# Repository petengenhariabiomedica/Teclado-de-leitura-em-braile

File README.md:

# Teclado-de-leitura-em-braile
Projeto de tecnologia assistiva voltado para pessoas cegas, consiste em um teclado que reproduzirá palavras da tela de um computador em letras em braile.

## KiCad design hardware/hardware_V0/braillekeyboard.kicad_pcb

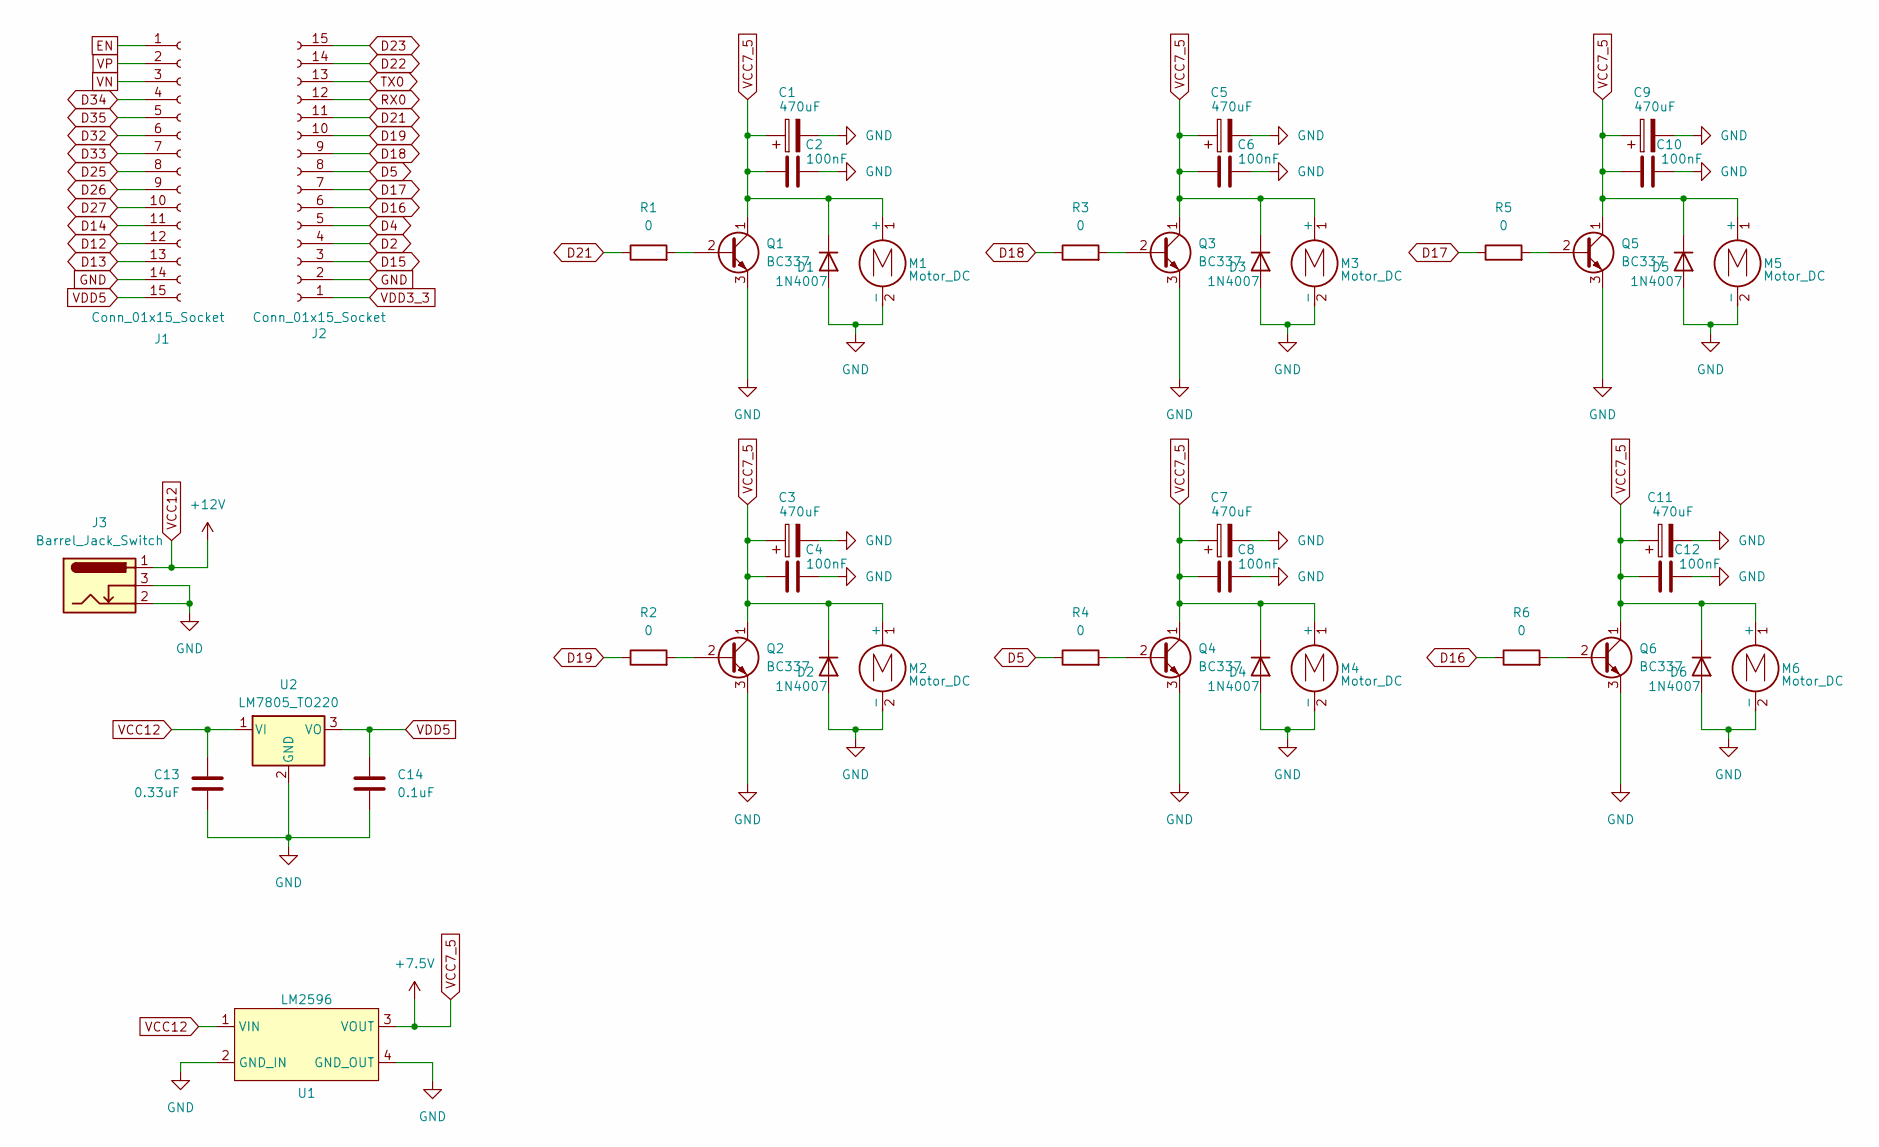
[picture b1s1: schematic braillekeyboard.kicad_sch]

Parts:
C1, C3, C5, C7, C9, C11: 470uF; CAPPRD500W60D1050H1750
C2, C4, C6, C8, C10, C12: 100nF; 615R100GAD10
C13: 0.33uF; CAPPRD350W60D825H1300
C14: 0.1uF; 615R100GAD10
D1, D2, D3, D4, D5, D6: 1N4007; D_DO-41_SOD81_P10.16mm_Horizontal
J1, J2: Conn_01x15_Socket; PinSocket_1x15_P2.54mm_Vertical
J3: Barrel_Jack_Switch; BarrelJack_Horizontal
M1, M2, M3, M4, M5, M6: Motor_DC; JST_XH_B2B-XH-AM_1x02_P2.50mm_Vertical
Q1, Q2, Q3, Q4, Q5, Q6: BC337; BC33716TA
R1, R2, R3, R4, R5, R6: 0; R_Axial_DIN0617_L17.0mm_D6.0mm_P25.40mm_Horizontal
U1: LM2596; LM2596_Module
U2: LM7805_TO220; TO-220-3_Vertical

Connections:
D2: J2.4
D4: J2.5
D5: J2.8, R4.1
D12: J1.12
D13: J1.13
D14: J1.11
D15: J2.3
D16: J2.6, R6.1
D17: J2.7, R5.1
D18: J2.9, R3.1
D19: J2.10, R2.1
D21: J2.11, R1.1
D22: J2.14
D23: J2.15
D25: J1.8
D26: J1.9
D27: J1.10
D32: J1.6
D33: J1.7
D34: J1.4
D35: J1.5
EN: J1.1
GND: C1.2, C2.2, C3.2, C4.2, C5.2, C6.2, C7.2, C8.2, C9.2, C10.2, C11.2, C12.2, C13.2, C14.2, D1.2 (A), D2.2 (A), D3.2 (A), D4.2 (A), D5.2 (A), D6.2 (A), J1.14, J2.2, J3.2, J3.3, M1.2 (-), M2.2 (-), M3.2 (-), M4.2 (-), M5.2 (-), M6.2 (-), Q1.3 (E), Q2.3 (E), Q3.3 (E), Q4.3 (E), Q5.3 (E), Q6.3 (E), U1.2 (GND_IN), U1.4 (GND_OUT), U2.2 (GND)
unnamed: Q1.2 (B), R1.2
unnamed: Q2.2 (B), R2.2
unnamed: Q3.2 (B), R3.2
unnamed: Q4.2 (B), R4.2
unnamed: Q5.2 (B), R5.2
unnamed: Q6.2 (B), R6.2
RX0: J2.12
TX0: J2.13
VCC7_5: C1.1, C2.1, C3.1, C4.1, C5.1, C6.1, C7.1, C8.1, C9.1, C10.1, C11.1, C12.1, D1.1 (K), D2.1 (K), D3.1 (K), D4.1 (K), D5.1 (K), D6.1 (K), M1.1 (+), M2.1 (+), M3.1 (+), M4.1 (+), M5.1 (+), M6.1 (+), Q1.1 (C), Q2.1 (C), Q3.1 (C), Q4.1 (C), Q5.1 (C), Q6.1 (C), U1.3 (VOUT)
VCC12: C13.1, J3.1, U1.1 (VIN), U2.1 (VI)
VDD3_3: J2.1
VDD5: C14.1, J1.15, U2.3 (VO)
VN: J1.3
VP: J1.2

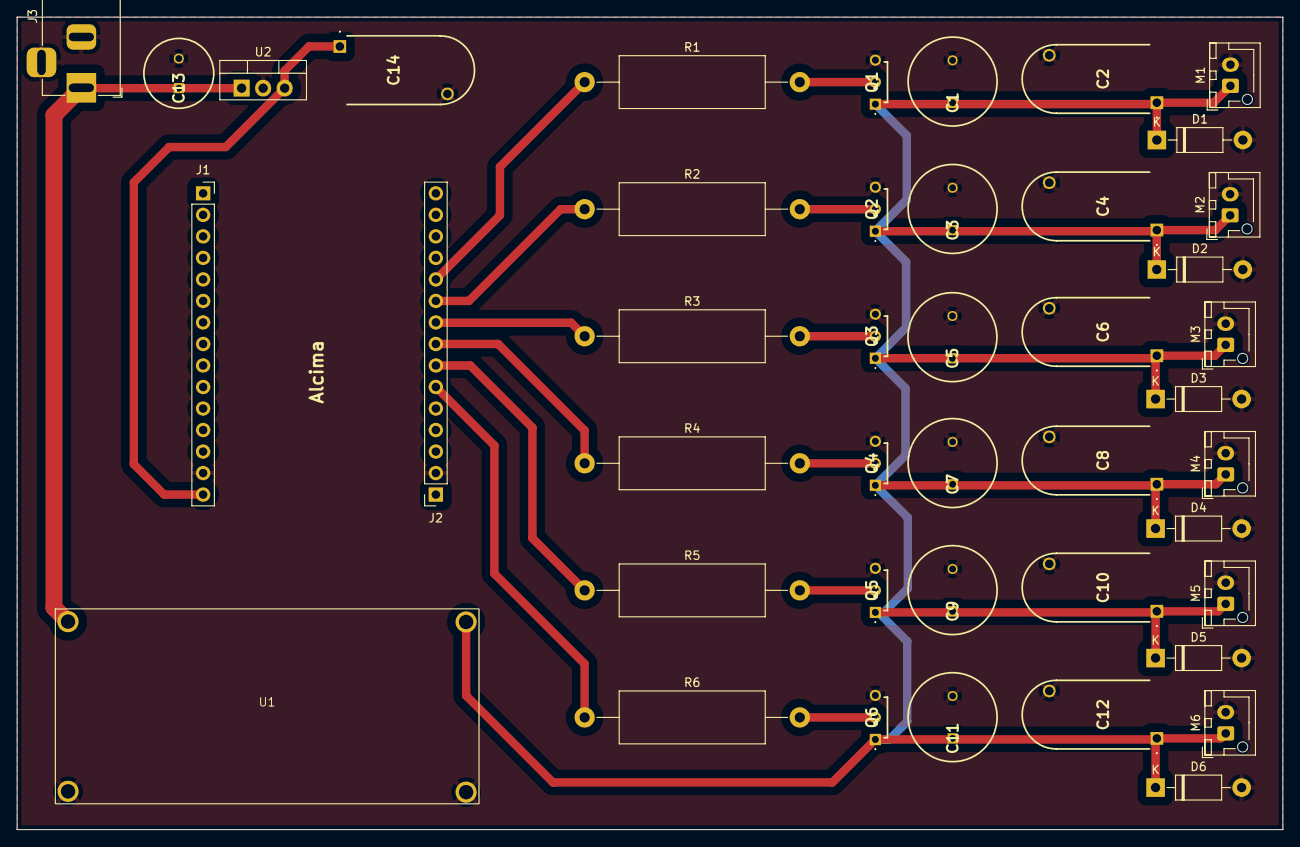
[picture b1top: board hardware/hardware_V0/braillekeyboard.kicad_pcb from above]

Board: 2 copper layers, 149.4 x 95.9 mm, 43 parts (0 on the bottom side), 16 nets.

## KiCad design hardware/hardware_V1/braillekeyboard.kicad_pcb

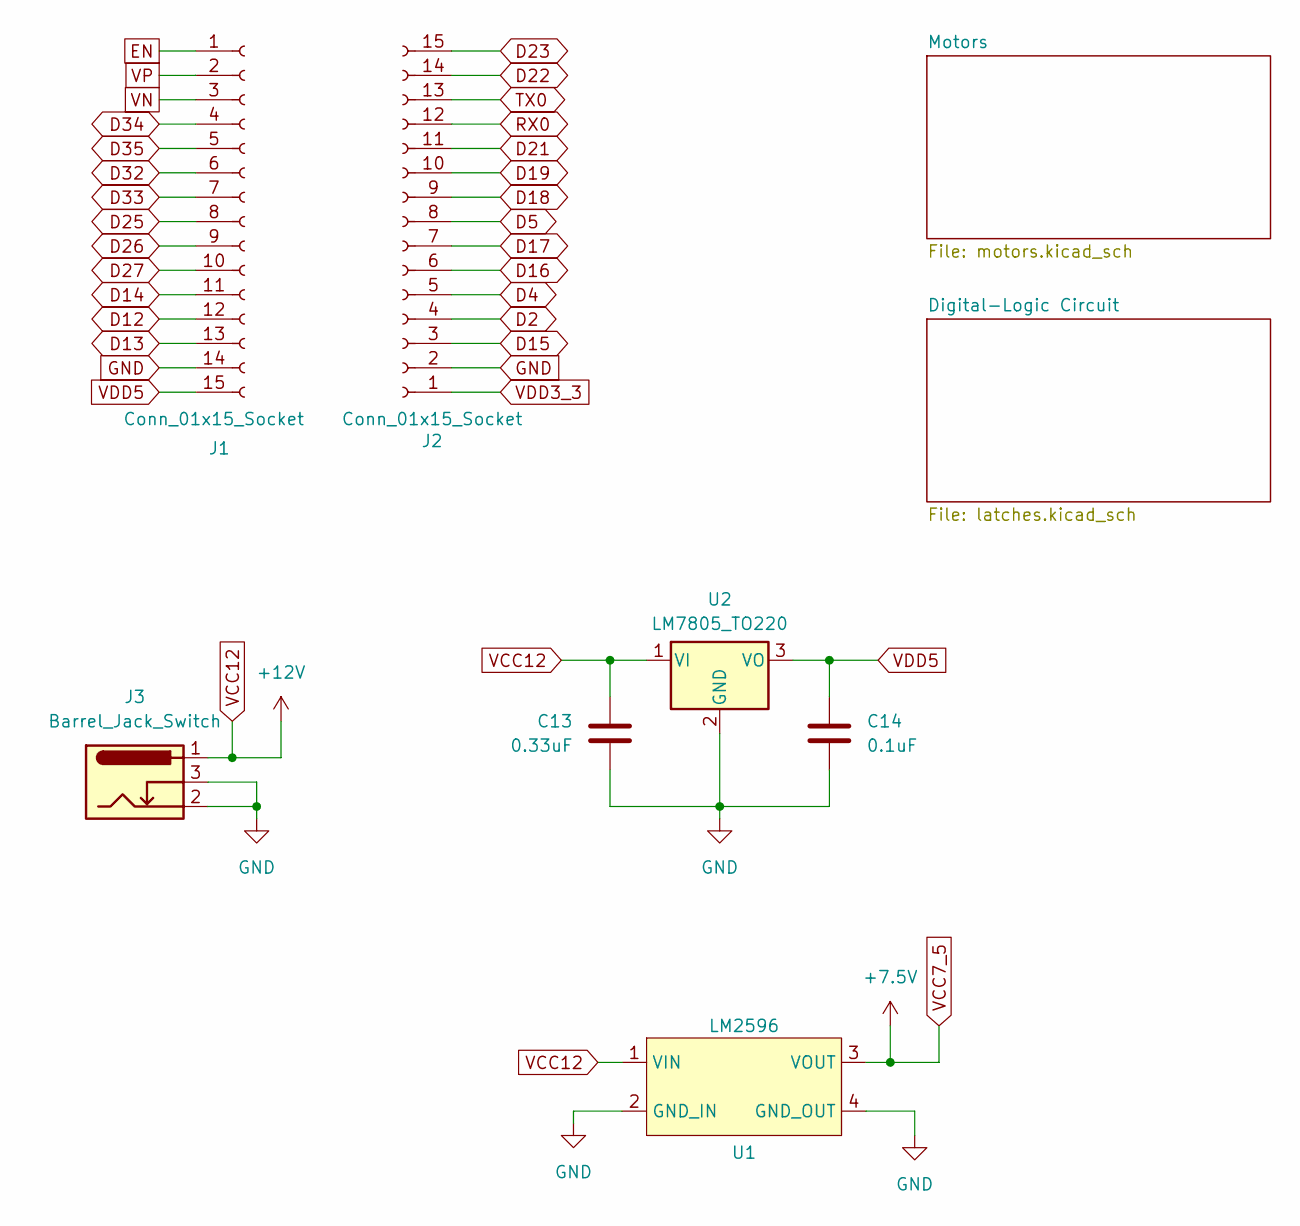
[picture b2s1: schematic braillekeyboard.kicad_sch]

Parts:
C13: 0.33uF; CAPPRD350W60D825H1300
C14: 0.1uF; 615R100GAD10
J1, J2: Conn_01x15_Socket; PinSocket_1x15_P2.54mm_Vertical
J3: Barrel_Jack_Switch; BarrelJack_Horizontal
U1: LM2596; LM2596_Module
U2: LM7805_TO220; TO-220-3_Vertical

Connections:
D2: J2.4; also elsewhere on the board
D4: J2.5; also elsewhere on the board
D5: J2.8; also elsewhere on the board
D12: J1.12; also elsewhere on the board
D13: J1.13; also elsewhere on the board
D14: J1.11; also elsewhere on the board
D15: J2.3; also elsewhere on the board
D16: J2.6; also elsewhere on the board
D17: J2.7; also elsewhere on the board
D18: J2.9; also elsewhere on the board
D19: J2.10; also elsewhere on the board
D21: J2.11; also elsewhere on the board
D22: J2.14
D23: J2.15
D25: J1.8; also elsewhere on the board
D26: J1.9; also elsewhere on the board
D27: J1.10; also elsewhere on the board
D32: J1.6
D33: J1.7; also elsewhere on the board
D34: J1.4
D35: J1.5
EN: J1.1
GND: C13.2, C14.2, J1.14, J2.2, J3.2, J3.3, U1.2 (GND_IN), U1.4 (GND_OUT), U2.2 (GND); also elsewhere on the board
RX0: J2.12
TX0: J2.13
VCC7_5: U1.3 (VOUT); also elsewhere on the board
VCC12: C13.1, J3.1, U1.1 (VIN), U2.1 (VI)
VDD3_3: J2.1
VDD5: C14.1, J1.15, U2.3 (VO); also elsewhere on the board
VN: J1.3
VP: J1.2

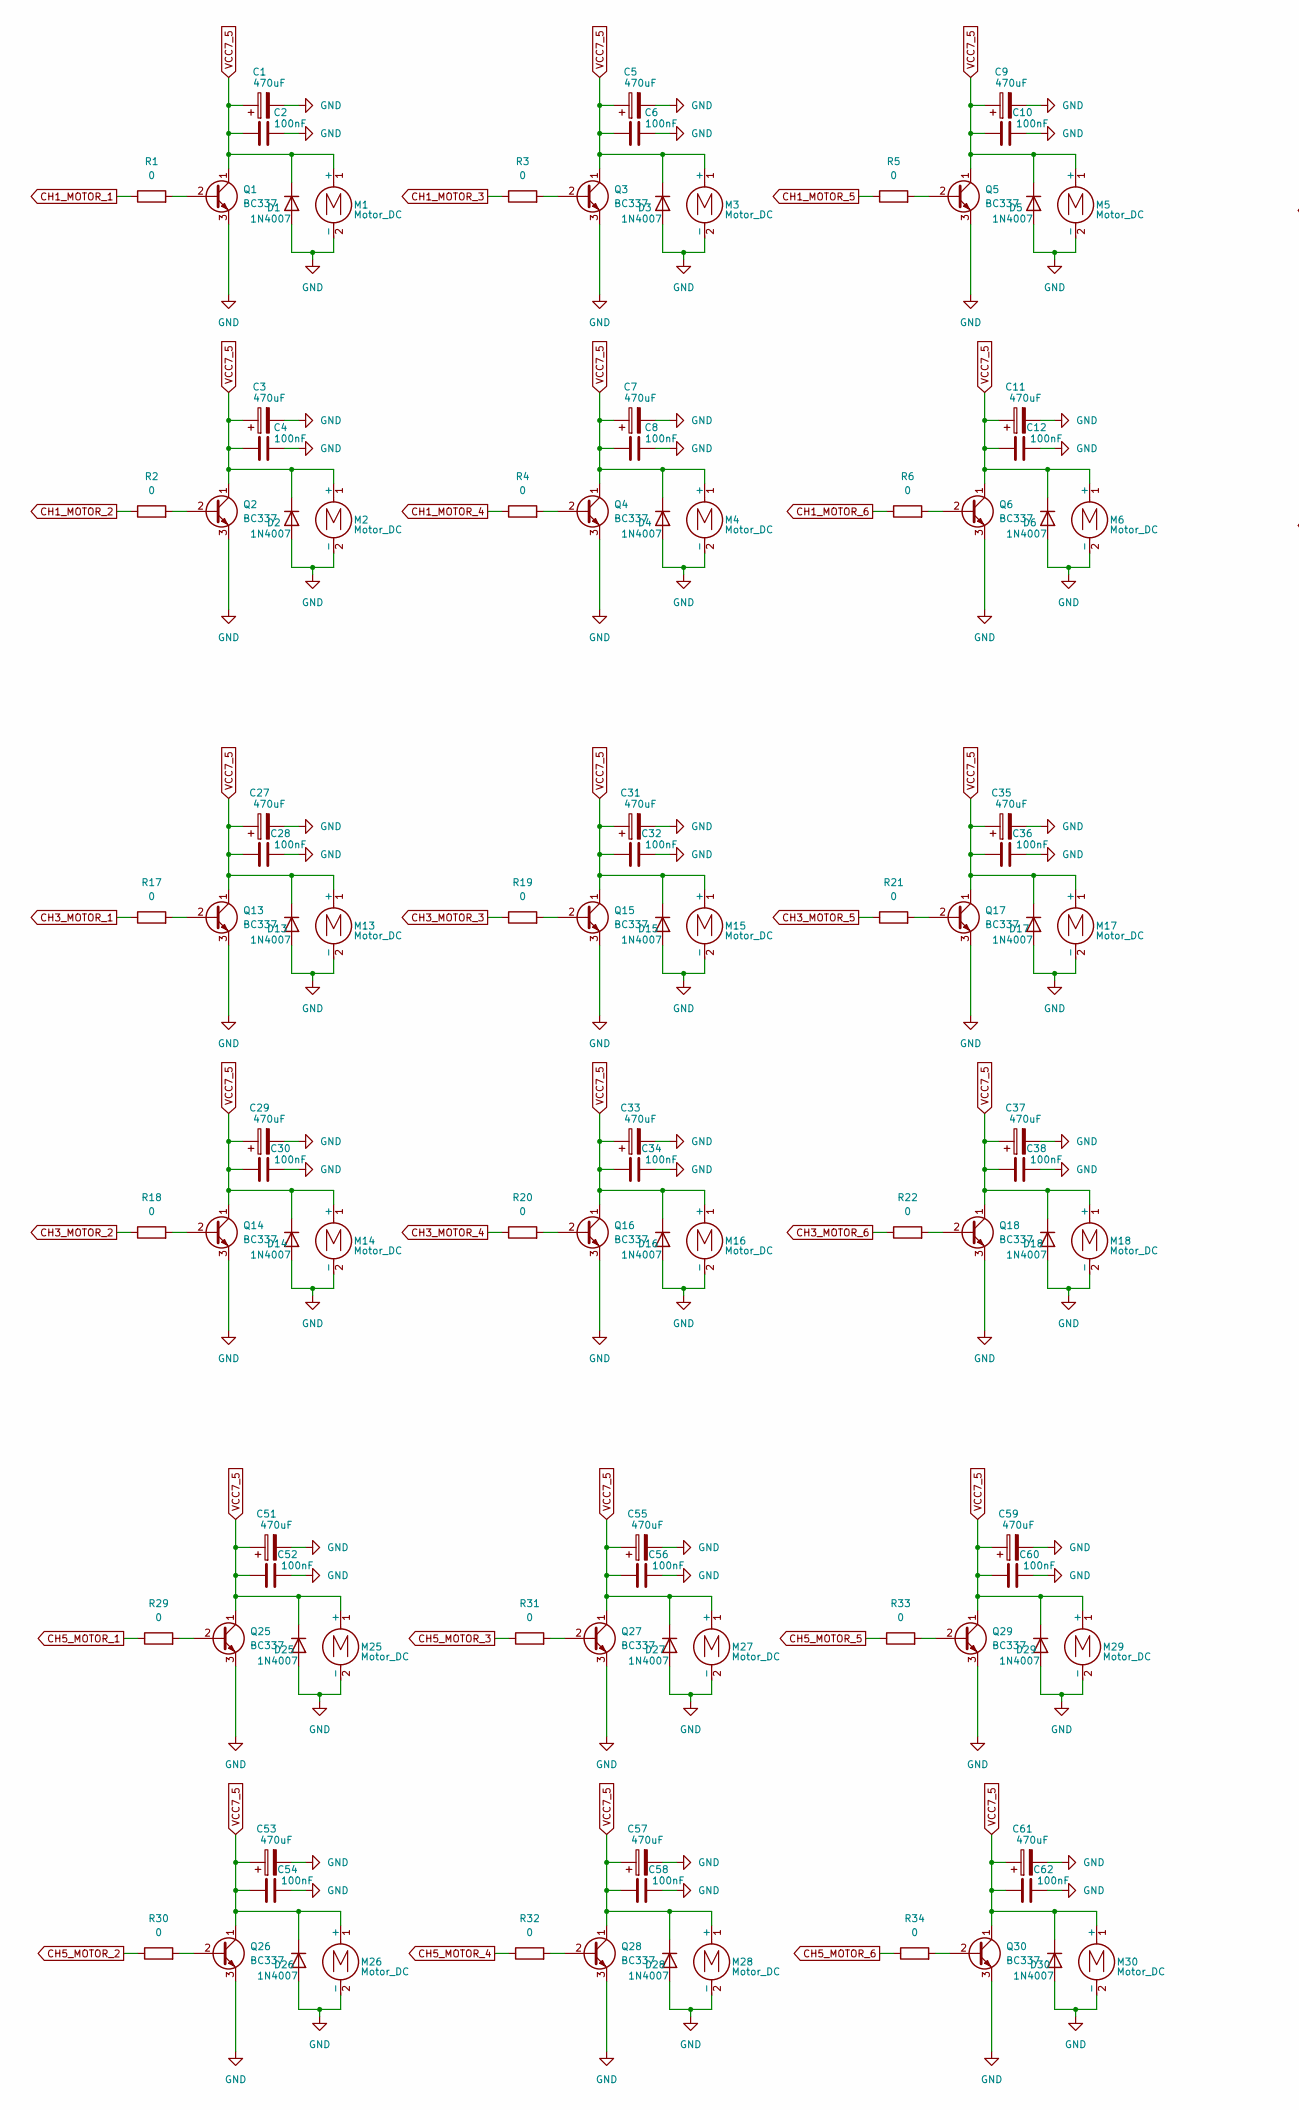
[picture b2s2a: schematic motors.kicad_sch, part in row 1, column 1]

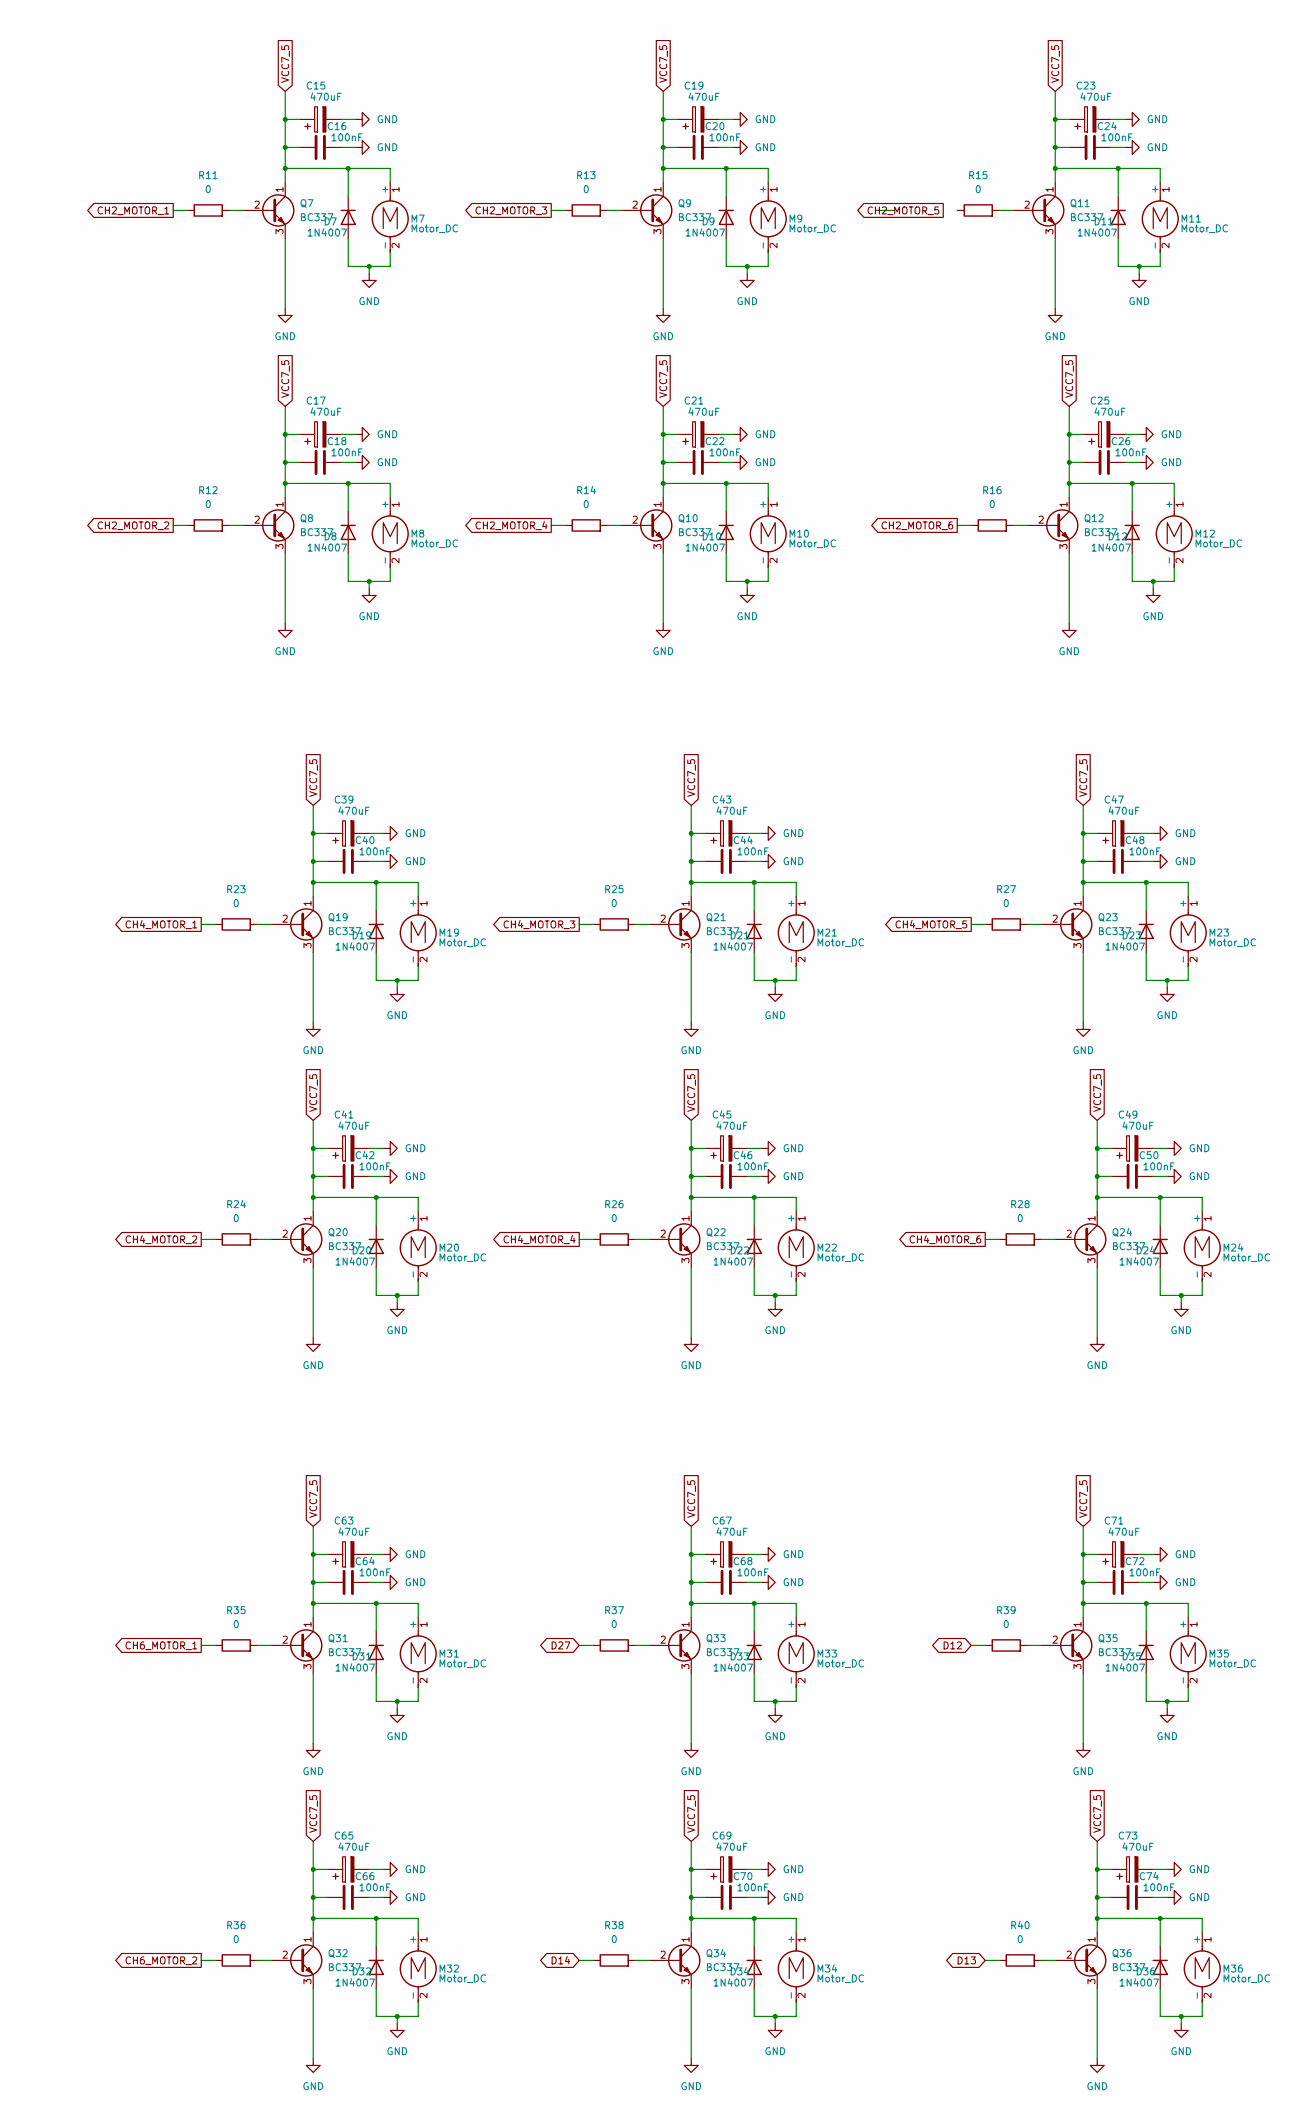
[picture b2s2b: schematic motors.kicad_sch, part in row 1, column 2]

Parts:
C1, C3, C5, C7, C9, C11, C15, C17, C19, C21, C23, C25, C27, C29, C31, C33, C35, C37, C39, C41, C43, C45, C47, C49, C51, C53, C55, C57, C59, C61, C63, C65, C67, C69, C71, C73: 470uF; CAPPRD500W60D1050H1750
C2, C4, C6, C8, C10, C12, C16, C18, C20, C22, C24, C26, C28, C30, C32, C34, C36, C38, C40, C42, C44, C46, C48, C50, C52, C54, C56, C58, C60, C62, C64, C66, C68, C70, C72, C74: 100nF; 615R100GAD10
D1, D2, D3, D4, D5, D6, D7, D8, D9, D10, D11, D12, D13, D14, D15, D16, D17, D18, D19, D20, D21, D22, D23, D24, D25, D26, D27, D28, D29, D30, D31, D32, D33, D34, D35, D36: 1N4007; D_DO-41_SOD81_P10.16mm_Horizontal
M1, M2, M3, M4, M5, M6, M7, M8, M9, M10, M11, M12, M13, M14, M15, M16, M17, M18, M19, M20, M21, M22, M23, M24, M25, M26, M27, M28, M29, M30, M31, M32, M33, M34, M35, M36: Motor_DC; JST_XH_B2B-XH-AM_1x02_P2.50mm_Vertical
Q1, Q2, Q3, Q4, Q5, Q6, Q7, Q8, Q9, Q10, Q11, Q12, Q13, Q14, Q15, Q16, Q17, Q18, Q19, Q20, Q21, Q22, Q23, Q24, Q25, Q26, Q27, Q28, Q29, Q30, Q31, Q32, Q33, Q34, Q35, Q36: BC337; BC33716TA
R1, R2, R3, R4, R5, R6, R11, R12, R13, R14, R15, R16, R17, R18, R19, R20, R21, R22, R23, R24, R25, R26, R27, R28, R29, R30, R31, R32, R33, R34, R35, R36, R37, R38, R39, R40: 0; R_Axial_DIN0617_L17.0mm_D6.0mm_P25.40mm_Horizontal

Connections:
CH1_MOTOR_1: R1.1; also elsewhere on the board
CH1_MOTOR_2: R2.1; also elsewhere on the board
CH1_MOTOR_3: R3.1; also elsewhere on the board
CH1_MOTOR_4: R4.1; also elsewhere on the board
CH1_MOTOR_5: R5.1; also elsewhere on the board
CH1_MOTOR_6: R6.1; also elsewhere on the board
CH2_MOTOR_1: R11.1; also elsewhere on the board
CH2_MOTOR_2: R12.1; also elsewhere on the board
CH2_MOTOR_3: R13.1; also elsewhere on the board
CH2_MOTOR_4: R14.1; also elsewhere on the board
CH2_MOTOR_6: R16.1; also elsewhere on the board
CH3_MOTOR_1: R17.1; also elsewhere on the board
CH3_MOTOR_2: R18.1; also elsewhere on the board
CH3_MOTOR_3: R19.1; also elsewhere on the board
CH3_MOTOR_4: R20.1; also elsewhere on the board
CH3_MOTOR_5: R21.1; also elsewhere on the board
CH3_MOTOR_6: R22.1; also elsewhere on the board
CH4_MOTOR_1: R23.1; also elsewhere on the board
CH4_MOTOR_2: R24.1; also elsewhere on the board
CH4_MOTOR_3: R25.1; also elsewhere on the board
CH4_MOTOR_4: R26.1; also elsewhere on the board
CH4_MOTOR_5: R27.1; also elsewhere on the board
CH4_MOTOR_6: R28.1; also elsewhere on the board
CH5_MOTOR_1: R29.1; also elsewhere on the board
CH5_MOTOR_2: R30.1; also elsewhere on the board
CH5_MOTOR_3: R31.1; also elsewhere on the board
CH5_MOTOR_4: R32.1; also elsewhere on the board
CH5_MOTOR_5: R33.1; also elsewhere on the board
CH5_MOTOR_6: R34.1; also elsewhere on the board
CH6_MOTOR_1: R35.1; also elsewhere on the board
CH6_MOTOR_2: R36.1; also elsewhere on the board
D12: R39.1; also elsewhere on the board
D13: R40.1; also elsewhere on the board
D14: R38.1; also elsewhere on the board
D27: R37.1; also elsewhere on the board
GND: C1.2, C2.2, C3.2, C4.2, C5.2, C6.2, C7.2, C8.2, C9.2, C10.2, C11.2, C12.2, C15.2, C16.2, C17.2, C18.2, C19.2, C20.2, C21.2, C22.2, C23.2, C24.2, C25.2, C26.2, C27.2, C28.2, C29.2, C30.2, C31.2, C32.2, C33.2, C34.2, C35.2, C36.2, C37.2, C38.2, C39.2, C40.2, C41.2, C42.2, C43.2, C44.2, C45.2, C46.2, C47.2, C48.2, C49.2, C50.2, C51.2, C52.2, C53.2, C54.2, C55.2, C56.2, C57.2, C58.2, C59.2, C60.2, C61.2, C62.2, C63.2, C64.2, C65.2, C66.2, C67.2, C68.2, C69.2, C70.2, C71.2, C72.2, C73.2, C74.2, D1.2 (A), D2.2 (A), D3.2 (A), D4.2 (A), D5.2 (A), D6.2 (A), D7.2 (A), D8.2 (A), D9.2 (A), D10.2 (A), D11.2 (A), D12.2 (A), D13.2 (A), D14.2 (A), D15.2 (A), D16.2 (A), D17.2 (A), D18.2 (A), D19.2 (A), D20.2 (A), D21.2 (A), D22.2 (A), D23.2 (A), D24.2 (A), D25.2 (A), D26.2 (A), D27.2 (A), D28.2 (A), D29.2 (A), D30.2 (A), D31.2 (A), D32.2 (A), D33.2 (A), D34.2 (A), D35.2 (A), D36.2 (A), M1.2 (-), M2.2 (-), M3.2 (-), M4.2 (-), M5.2 (-), M6.2 (-), M7.2 (-), M8.2 (-), M9.2 (-), M10.2 (-), M11.2 (-), M12.2 (-), M13.2 (-), M14.2 (-), M15.2 (-), M16.2 (-), M17.2 (-), M18.2 (-), M19.2 (-), M20.2 (-), M21.2 (-), M22.2 (-), M23.2 (-), M24.2 (-), M25.2 (-), M26.2 (-), M27.2 (-), M28.2 (-), M29.2 (-), M30.2 (-), M31.2 (-), M32.2 (-), M33.2 (-), M34.2 (-), M35.2 (-), M36.2 (-), Q1.3 (E), Q2.3 (E), Q3.3 (E), Q4.3 (E), Q5.3 (E), Q6.3 (E), Q7.3 (E), Q8.3 (E), Q9.3 (E), Q10.3 (E), Q11.3 (E), Q12.3 (E), Q13.3 (E), Q14.3 (E), Q15.3 (E), Q16.3 (E), Q17.3 (E), Q18.3 (E), Q19.3 (E), Q20.3 (E), Q21.3 (E), Q22.3 (E), Q23.3 (E), Q24.3 (E), Q25.3 (E), Q26.3 (E), Q27.3 (E), Q28.3 (E), Q29.3 (E), Q30.3 (E), Q31.3 (E), Q32.3 (E), Q33.3 (E), Q34.3 (E), Q35.3 (E), Q36.3 (E); also elsewhere on the board
unnamed: Q1.2 (B), R1.2
unnamed: Q2.2 (B), R2.2
unnamed: Q3.2 (B), R3.2
unnamed: Q4.2 (B), R4.2
unnamed: Q5.2 (B), R5.2
unnamed: Q6.2 (B), R6.2
unnamed: Q7.2 (B), R11.2
unnamed: Q8.2 (B), R12.2
unnamed: Q9.2 (B), R13.2
unnamed: Q10.2 (B), R14.2
unnamed: Q11.2 (B), R15.2
unnamed: Q12.2 (B), R16.2
unnamed: Q13.2 (B), R17.2
unnamed: Q14.2 (B), R18.2
unnamed: Q15.2 (B), R19.2
unnamed: Q16.2 (B), R20.2
unnamed: Q17.2 (B), R21.2
unnamed: Q18.2 (B), R22.2
unnamed: Q19.2 (B), R23.2
unnamed: Q20.2 (B), R24.2
unnamed: Q21.2 (B), R25.2
unnamed: Q22.2 (B), R26.2
unnamed: Q23.2 (B), R27.2
unnamed: Q24.2 (B), R28.2
unnamed: Q25.2 (B), R29.2
unnamed: Q26.2 (B), R30.2
unnamed: Q27.2 (B), R31.2
unnamed: Q28.2 (B), R32.2
unnamed: Q29.2 (B), R33.2
unnamed: Q30.2 (B), R34.2
unnamed: Q31.2 (B), R35.2
unnamed: Q32.2 (B), R36.2
unnamed: Q33.2 (B), R37.2
unnamed: Q34.2 (B), R38.2
unnamed: Q35.2 (B), R39.2
unnamed: Q36.2 (B), R40.2
VCC7_5: C1.1, C2.1, C3.1, C4.1, C5.1, C6.1, C7.1, C8.1, C9.1, C10.1, C11.1, C12.1, C15.1, C16.1, C17.1, C18.1, C19.1, C20.1, C21.1, C22.1, C23.1, C24.1, C25.1, C26.1, C27.1, C28.1, C29.1, C30.1, C31.1, C32.1, C33.1, C34.1, C35.1, C36.1, C37.1, C38.1, C39.1, C40.1, C41.1, C42.1, C43.1, C44.1, C45.1, C46.1, C47.1, C48.1, C49.1, C50.1, C51.1, C52.1, C53.1, C54.1, C55.1, C56.1, C57.1, C58.1, C59.1, C60.1, C61.1, C62.1, C63.1, C64.1, C65.1, C66.1, C67.1, C68.1, C69.1, C70.1, C71.1, C72.1, C73.1, C74.1, D1.1 (K), D2.1 (K), D3.1 (K), D4.1 (K), D5.1 (K), D6.1 (K), D7.1 (K), D8.1 (K), D9.1 (K), D10.1 (K), D11.1 (K), D12.1 (K), D13.1 (K), D14.1 (K), D15.1 (K), D16.1 (K), D17.1 (K), D18.1 (K), D19.1 (K), D20.1 (K), D21.1 (K), D22.1 (K), D23.1 (K), D24.1 (K), D25.1 (K), D26.1 (K), D27.1 (K), D28.1 (K), D29.1 (K), D30.1 (K), D31.1 (K), D32.1 (K), D33.1 (K), D34.1 (K), D35.1 (K), D36.1 (K), M1.1 (+), M2.1 (+), M3.1 (+), M4.1 (+), M5.1 (+), M6.1 (+), M7.1 (+), M8.1 (+), M9.1 (+), M10.1 (+), M11.1 (+), M12.1 (+), M13.1 (+), M14.1 (+), M15.1 (+), M16.1 (+), M17.1 (+), M18.1 (+), M19.1 (+), M20.1 (+), M21.1 (+), M22.1 (+), M23.1 (+), M24.1 (+), M25.1 (+), M26.1 (+), M27.1 (+), M28.1 (+), M29.1 (+), M30.1 (+), M31.1 (+), M32.1 (+), M33.1 (+), M34.1 (+), M35.1 (+), M36.1 (+), Q1.1 (C), Q2.1 (C), Q3.1 (C), Q4.1 (C), Q5.1 (C), Q6.1 (C), Q7.1 (C), Q8.1 (C), Q9.1 (C), Q10.1 (C), Q11.1 (C), Q12.1 (C), Q13.1 (C), Q14.1 (C), Q15.1 (C), Q16.1 (C), Q17.1 (C), Q18.1 (C), Q19.1 (C), Q20.1 (C), Q21.1 (C), Q22.1 (C), Q23.1 (C), Q24.1 (C), Q25.1 (C), Q26.1 (C), Q27.1 (C), Q28.1 (C), Q29.1 (C), Q30.1 (C), Q31.1 (C), Q32.1 (C), Q33.1 (C), Q34.1 (C), Q35.1 (C), Q36.1 (C); also elsewhere on the board

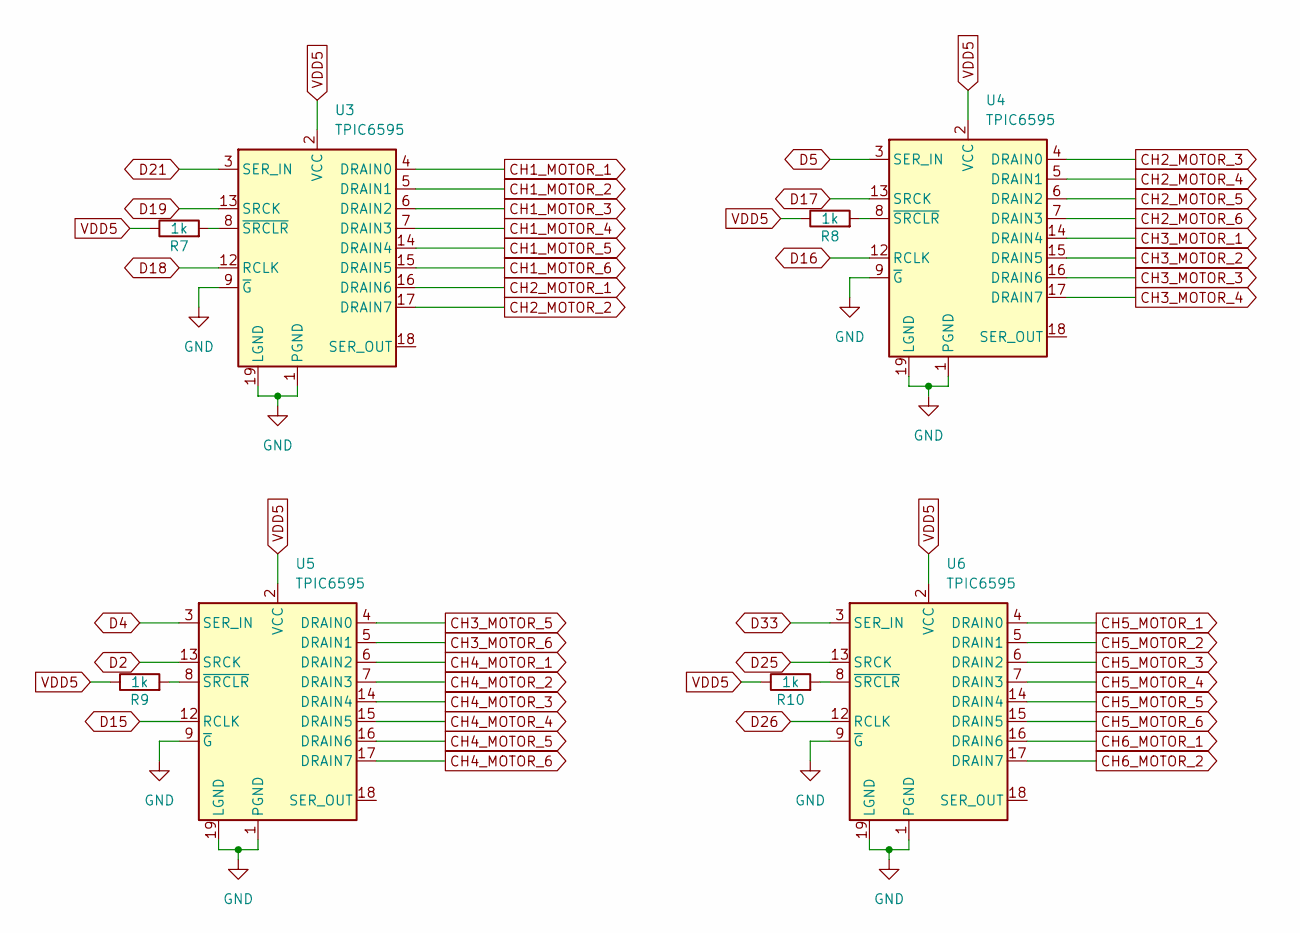
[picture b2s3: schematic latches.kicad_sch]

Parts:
R7, R8, R9, R10: 1k; R_Axial_DIN0617_L17.0mm_D6.0mm_P25.40mm_Horizontal
U3, U4, U5, U6: TPIC6595; DIP794W53P254L2540H508Q20N

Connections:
CH1_MOTOR_1: U3.4 (DRAIN0); also elsewhere on the board
CH1_MOTOR_2: U3.5 (DRAIN1); also elsewhere on the board
CH1_MOTOR_3: U3.6 (DRAIN2); also elsewhere on the board
CH1_MOTOR_4: U3.7 (DRAIN3); also elsewhere on the board
CH1_MOTOR_5: U3.14 (DRAIN4); also elsewhere on the board
CH1_MOTOR_6: U3.15 (DRAIN5); also elsewhere on the board
CH2_MOTOR_1: U3.16 (DRAIN6); also elsewhere on the board
CH2_MOTOR_2: U3.17 (DRAIN7); also elsewhere on the board
CH2_MOTOR_3: U4.4 (DRAIN0); also elsewhere on the board
CH2_MOTOR_4: U4.5 (DRAIN1); also elsewhere on the board
CH2_MOTOR_5: U4.6 (DRAIN2)
CH2_MOTOR_6: U4.7 (DRAIN3); also elsewhere on the board
CH3_MOTOR_1: U4.14 (DRAIN4); also elsewhere on the board
CH3_MOTOR_2: U4.15 (DRAIN5); also elsewhere on the board
CH3_MOTOR_3: U4.16 (DRAIN6); also elsewhere on the board
CH3_MOTOR_4: U4.17 (DRAIN7); also elsewhere on the board
CH3_MOTOR_5: U5.4 (DRAIN0); also elsewhere on the board
CH3_MOTOR_6: U5.5 (DRAIN1); also elsewhere on the board
CH4_MOTOR_1: U5.6 (DRAIN2); also elsewhere on the board
CH4_MOTOR_2: U5.7 (DRAIN3); also elsewhere on the board
CH4_MOTOR_3: U5.14 (DRAIN4); also elsewhere on the board
CH4_MOTOR_4: U5.15 (DRAIN5); also elsewhere on the board
CH4_MOTOR_5: U5.16 (DRAIN6); also elsewhere on the board
CH4_MOTOR_6: U5.17 (DRAIN7); also elsewhere on the board
CH5_MOTOR_1: U6.4 (DRAIN0); also elsewhere on the board
CH5_MOTOR_2: U6.5 (DRAIN1); also elsewhere on the board
CH5_MOTOR_3: U6.6 (DRAIN2); also elsewhere on the board
CH5_MOTOR_4: U6.7 (DRAIN3); also elsewhere on the board
CH5_MOTOR_5: U6.14 (DRAIN4); also elsewhere on the board
CH5_MOTOR_6: U6.15 (DRAIN5); also elsewhere on the board
CH6_MOTOR_1: U6.16 (DRAIN6); also elsewhere on the board
CH6_MOTOR_2: U6.17 (DRAIN7); also elsewhere on the board
D2: U5.13 (SRCK); also elsewhere on the board
D4: U5.3 (SER_IN); also elsewhere on the board
D5: U4.3 (SER_IN); also elsewhere on the board
D15: U5.12 (RCLK); also elsewhere on the board
D16: U4.12 (RCLK); also elsewhere on the board
D17: U4.13 (SRCK); also elsewhere on the board
D18: U3.12 (RCLK); also elsewhere on the board
D19: U3.13 (SRCK); also elsewhere on the board
D21: U3.3 (SER_IN); also elsewhere on the board
D25: U6.13 (SRCK); also elsewhere on the board
D26: U6.12 (RCLK); also elsewhere on the board
D33: U6.3 (SER_IN); also elsewhere on the board
GND: U3.1 (PGND), U3.9 (~G), U3.10 (PGND), U3.11 (PGND), U3.19 (LGND), U3.20 (PGND), U4.1 (PGND), U4.9 (~G), U4.10 (PGND), U4.11 (PGND), U4.19 (LGND), U4.20 (PGND), U5.1 (PGND), U5.9 (~G), U5.10 (PGND), U5.11 (PGND), U5.19 (LGND), U5.20 (PGND), U6.1 (PGND), U6.9 (~G), U6.10 (PGND), U6.11 (PGND), U6.19 (LGND), U6.20 (PGND); also elsewhere on the board
unnamed: R7.2, U3.8 (~SRCLR)
unnamed: R8.2, U4.8 (~SRCLR)
unnamed: R9.2, U5.8 (~SRCLR)
unnamed: R10.2, U6.8 (~SRCLR)
VDD5: R7.1, R8.1, R9.1, R10.1, U3.2 (VCC), U4.2 (VCC), U5.2 (VCC), U6.2 (VCC); also elsewhere on the board

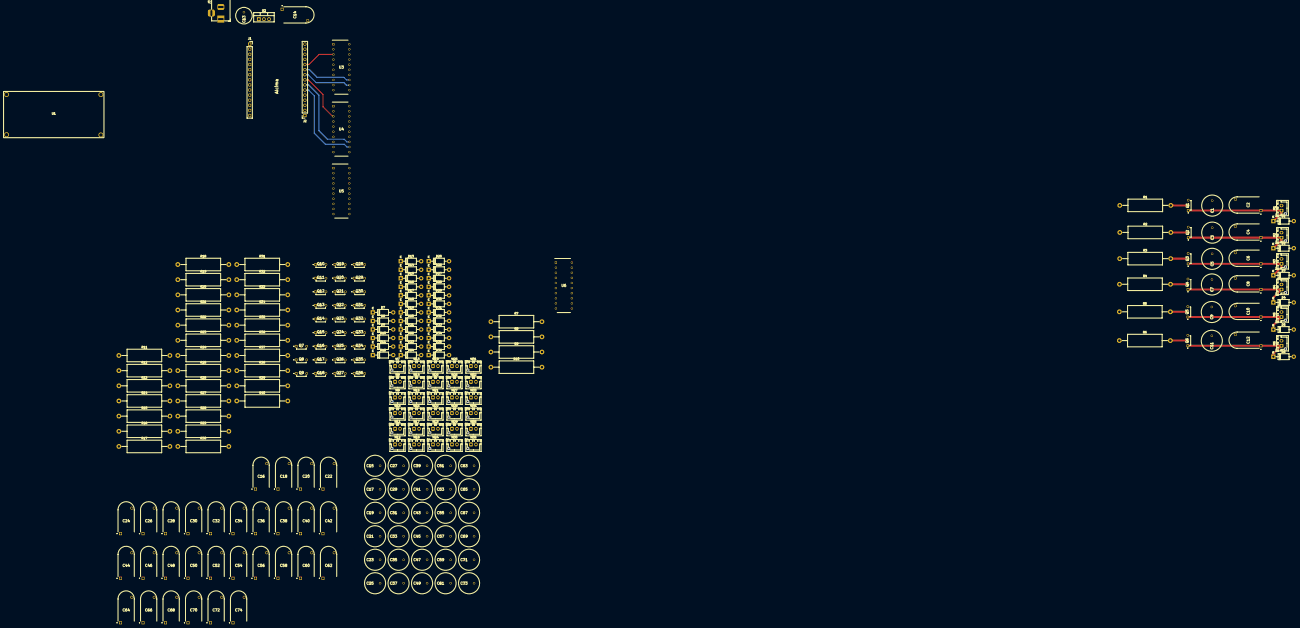
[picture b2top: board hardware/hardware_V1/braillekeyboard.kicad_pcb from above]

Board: 2 copper layers, 231 parts (0 on the bottom side), 91 nets.

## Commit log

2025-04-08 hardware para desenvolvimento do projeto
2025-04-08 Interface para gerar texto do PDF
2025-04-08 Interface para envio do PDF
2025-04-18 Gera um .txt a partir do PDF enviado + Firmware para receber texto
2025-04-19 Implementação do Firmware e Alterações na interface
2025-04-19 Atualização do Firmware para enviar OK em todos os casos
2025-04-19 Atualização da interface com GPT para corrigir texto antes de enviar para o ESP32
2025-04-21 Inclusão de caracteres especiais e modificações da interface
2025-04-21 Melhorias na interface
2025-04-21 Exclusão de firmware
2025-04-21 Exclusão do firmware
2025-04-21 Inclusão do Firmware final
2025-04-25 Correção do Firmware
2025-05-01 Firmware funcional com biblioteca de servos
2025-05-01 Interface atualizada
2025-07-08 Schematic inclusion
2025-07-20 adding gitignore
2025-07-20 Atualizações de interface e hardware
2025-07-20 Ajustes finais e atualização do .gitignore antes do pull
2025-07-20 Removendo pastas ignoradas que foram adicionadas por engano
2025-07-20 Firmware update
2025-07-20 Removendo pastas ignoradas do histórico da branch schematic
2025-07-20 update gitignore
2025-07-20 hardware atualizado
2025-07-24 Atualização dos footprints
2025-07-24 Reorganização dos componentes
2025-07-25 PCB layout v1
2025-07-26 Subdivisão do hardware para implementação da nova versão
2025-07-26 Nova versão do hardware
2025-07-26 Inclusão do latch no circuito, ampliação para 36 motores
